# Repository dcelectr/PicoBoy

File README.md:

# PicoBoy
PCB carrier board for a Raspberry Pi Pico that fits into a Mini Pocket Gameboy Handheld, based on a [twitter thread](https://twitter.com/wren6991/status/1436687829564854275) by Luke Wren.

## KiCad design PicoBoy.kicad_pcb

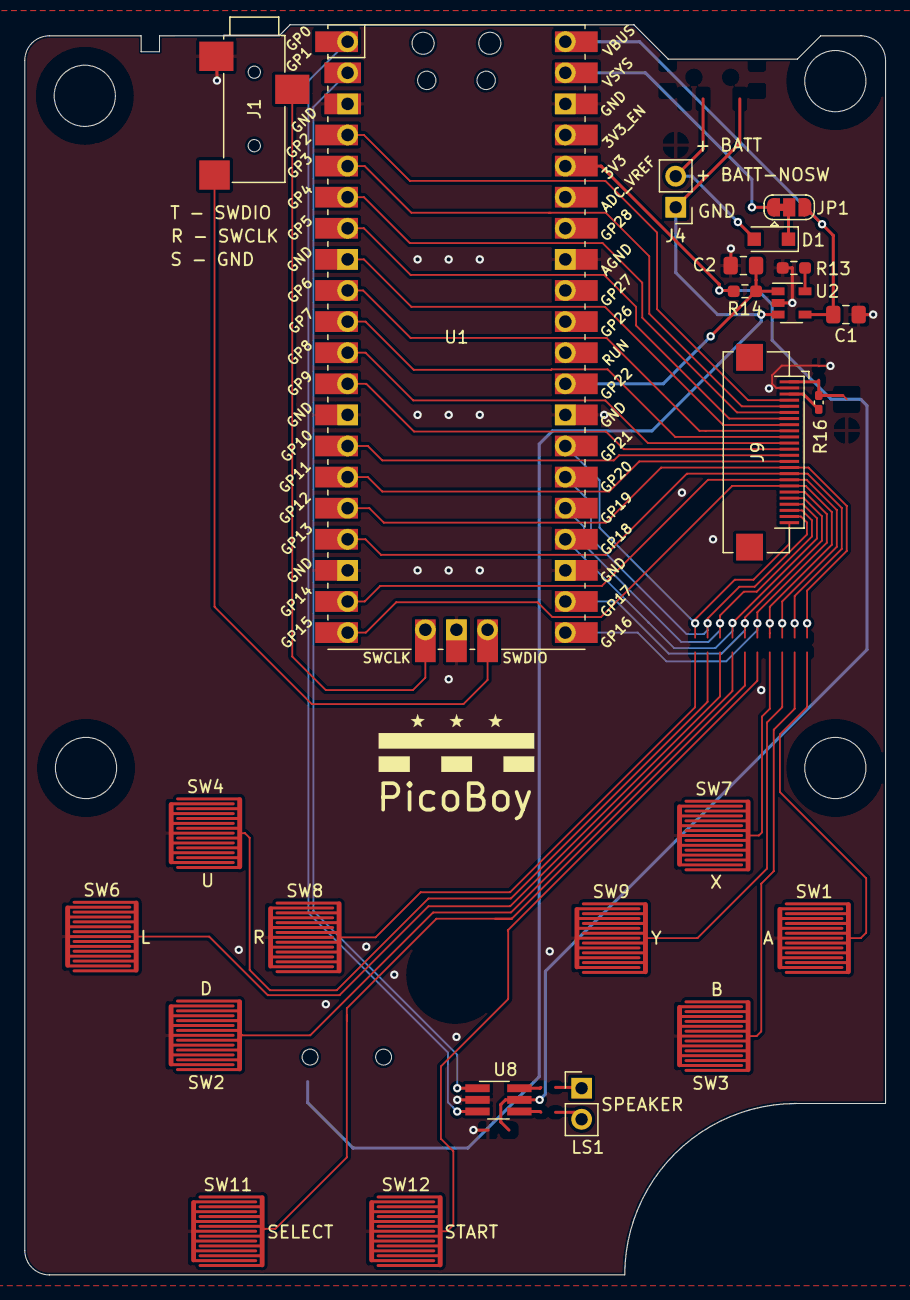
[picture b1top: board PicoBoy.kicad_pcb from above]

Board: 2 copper layers, 70.3 x 102.1 mm, 25 parts (1 on the bottom side), 34 nets.

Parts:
C1: 4.7uF; C_0805_2012Metric_Pad1.18x1.45mm_HandSolder
C2: 10uF; C_0805_2012Metric_Pad1.18x1.45mm_HandSolder
D1: MBR120; D_SOD-123F
J1: 2.5mm-3P-TRS; SJ-2523-SMT-TRS
J3: 1827928-1 TE; 1827928-1-battery
J4: 0.1; PinHeader_1x03_P2.54mm_Vertical
J9: 0.5mm FFC bottom-contact; FPC_24_0.5mm
JP1: SolderJumper_3_Bridged12; SolderJumper-3_P1.3mm_Bridged12_RoundedPad1.0x1.5mm
LS1: Speaker; PinHeader_1x02_P2.54mm_Vertical
R13: 5k; R_0603_1608Metric_Pad0.98x0.95mm_HandSolder
R14: 1k; R_0603_1608Metric_Pad0.98x0.95mm_HandSolder
R16: 27; C_0402_1005Metric_Pad0.74x0.62mm_HandSolder
SW1, SW2, SW3, SW4, SW6, SW7, SW8, SW9, SW11, SW12: memebrane; membrane-switch-6mm
U1: Pico; RPi_Pico_SMD_TH
U2: MCP73831-2-OT; SOT-23-5
U8: 74LVC2G04; TSOT-23-6_HandSoldering

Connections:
+3V3: J4.1, J9.1, R14.1, R16.1, U1.36, U8.5
+BATT: J3.1, U2.3
/BATT_STAT: C2.1, R14.2, U1.29, U2.1
/LCD_DB0: J9.9, U1.9
/LCD_DB1: J9.10, U1.10
/LCD_DB2: J9.11, U1.11
/LCD_DB3: J9.12, U1.12
/LCD_DB4: J9.13, U1.14
/LCD_DB5: J9.14, U1.15
/LCD_DB6: J9.15, U1.16
/LCD_DB7: J9.16, U1.17
/LCD_DB8: J9.17, U1.19
/LCD_DB9: J9.18, U1.20
/LCD_DB10: J9.19, U1.21
/LCD_DB11: J9.20, U1.22
/LCD_DB12: J9.21, U1.24
/LCD_DB13: J9.22, U1.25
/LCD_DB14: J9.23, U1.26
/LCD_DB15: J9.24, U1.27
/LCD_LED: J9.3, R16.2
/LCD_RS: J9.6, U1.6
/LCD_~CS: J9.5, U1.5
/LCD_~RD: J9.8, U1.8
/LCD_~RST: J9.4, U1.4
/LCD_~WR: J9.7, U1.7
/SPEAKER_PWM+: U1.2, U8.1
/SPEAKER_PWM-: U1.1, U8.3
/SWCLK: J1.R, U1.41
/SWDIO: J1.T, U1.43
/VSYS: JP1.1, U1.39
GND: C1.2, C2.2, J1.S, J3.3, J4.2, J9.2, R13.2, SW1.1, SW2.1, SW3.1, SW4.1, SW6.1, SW7.1, SW8.1, SW9.1, SW11.1, SW12.1, U1.3, U1.13, U1.18, U1.23, U1.28, U1.33, U1.38, U1.42, U2.2, U8.2
unnamed: D1.1, JP1.2
unnamed: R13.1, U2.5
VBUS: C1.1, JP1.3, U1.40, U2.4
